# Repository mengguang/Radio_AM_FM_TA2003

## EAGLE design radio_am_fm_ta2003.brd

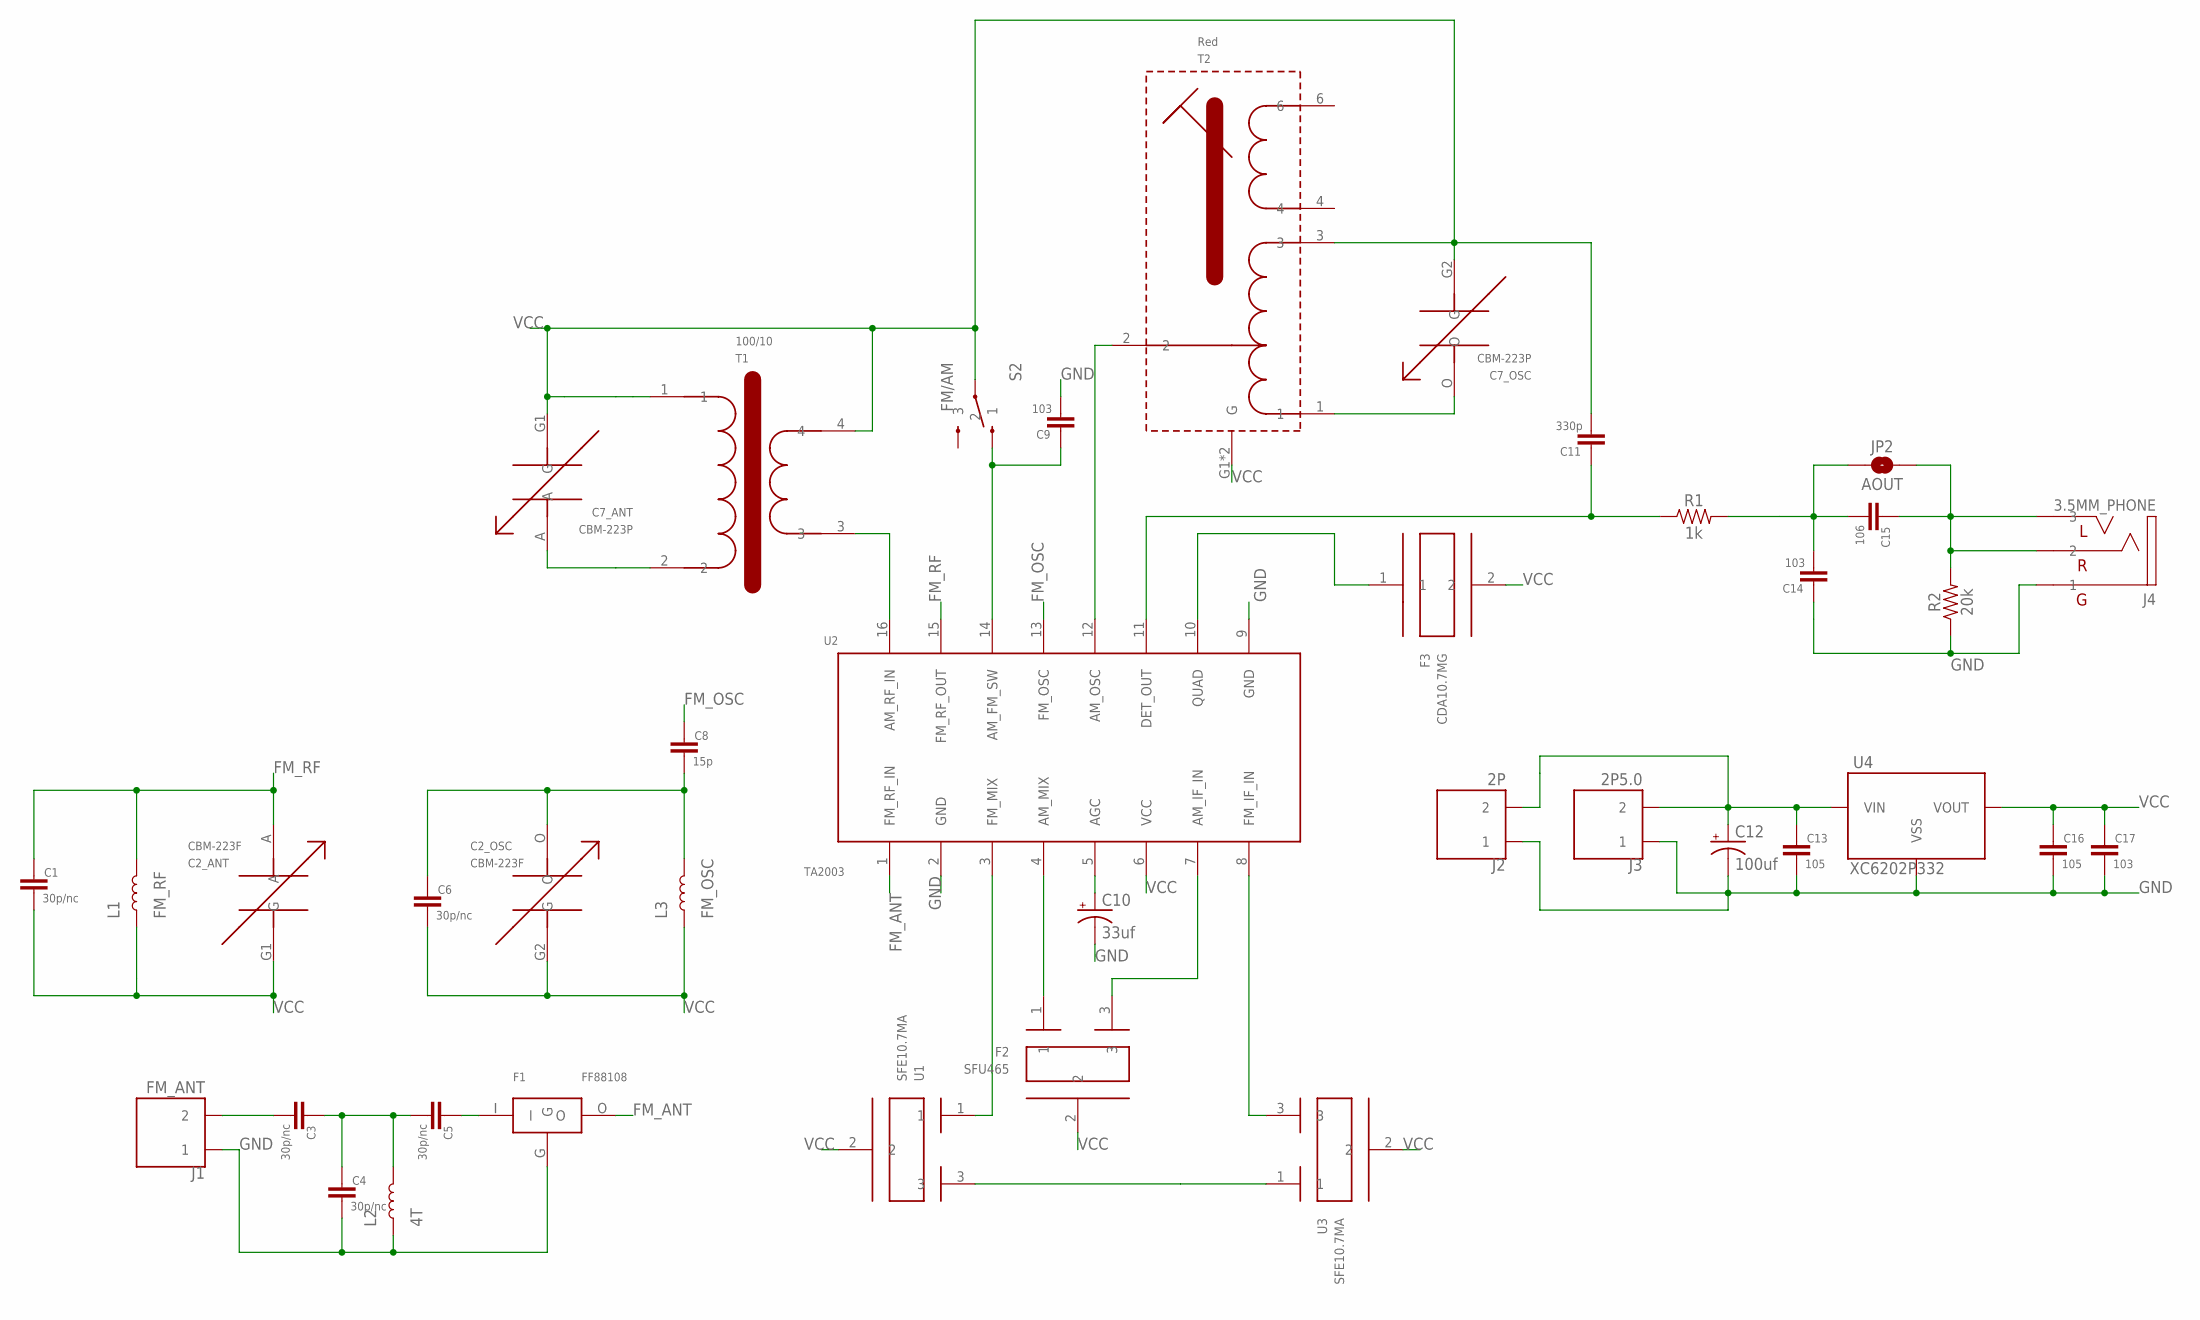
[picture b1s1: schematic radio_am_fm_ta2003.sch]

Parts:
C1, C3, C4, C5, C6: 30p/nc; C0603
C2: CBM-223F; CBM-223P
C7: CBM-223P
C8: 15p; C0603
C9, C14, C17: 103; C0603
C10: 33uf; CAP_2MM
C11: 330p; C0603
C12: 100uf; CAP_2.5MM
C13, C16: 105; C0603
C15: 106; C0603
F1: FF88108
F2: SFU465
F3: CDA10.7MG
J1: FM_ANT; 2P_2.54MM
J2: 2P; 2P_2.54MM
J3: 2P5.0; 2P_5.08MM
J4: 3.5MM_PHONE; 3.5MM
JP2: AOUT; SMT-JUMPER_2_NO_SILK
L1: FM_RF; VLU0810
L2: 4T; VLU0810
L3: FM_OSC; VLU0810
R1: 1k; R0603
R2: 20k; R0603
S2: FM/AM; L12.1_W5.6
T1: 100/10; AM_ANT_COIL
T2: Red; 42IF1XX
U1, U3: SFE10.7MA
U2: TA2003; DIP16
U4: XC6202P332; SOT-23-3

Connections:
FM_ANT: F1.O, U2.1 (FM_RF_IN)
FM_OSC: C8.1, U2.13 (FM_OSC)
FM_OSC1: C2.O, C6.1, C8.2, L3.- (2)
FM_RF: C1.1, C2.A, L1.- (2), U2.15 (FM_RF_OUT)
GND: C4.2, C9.2, C10.-, C12.-, C13.2, C14.1, C16.2, C17.2, F1.G, J1.1, J2.1, J3.L (1), J4.P$1 (1), L2.+ (1), R2.1, U2.2 (GND), U2.9 (GND), U4.3 (VSS)
unnamed: C7.O, T2.1
unnamed: T1.3, U2.16 (AM_RF_IN)
unnamed: C7.A, T1.2
unnamed: T2.2, U2.12 (AM_OSC)
unnamed: C11.1, R1.1, U2.11 (DET_OUT)
unnamed: C9.1, S2.1, U2.14 (AM_FM_SW)
unnamed: C10.+, U2.5 (AGC)
unnamed: F2.1, U2.4 (AM_MIX)
unnamed: F2.3, U2.7 (AM_IF_IN)
unnamed: U1.1, U2.3 (FM_MIX)
unnamed: U2.8 (FM_IF_IN), U3.3
unnamed: C15.1, J4.P$2 (2), J4.P$3 (3), JP2.2, R2.2
unnamed: U1.3, U3.1
unnamed: F3.1, U2.10 (QUAD)
unnamed: C3.1, C4.1, C5.2, L2.- (2)
unnamed: C3.2, J1.2
unnamed: C14.2, C15.2, JP2.1, R1.2
unnamed: C5.1, F1.I
unnamed: C12.+, C13.1, J2.2, J3.N (2), U4.2 (VIN)
VCC: C1.2, C2.G1 (G), C2.G2 (G), C6.2, C7.G1 (G), C7.G2 (G), C11.2, C16.1, C17.1, F2.2, F3.2, L1.+ (1), L3.+ (1), S2.2, T1.1, T1.4, T2.3, T2.G1 (G), T2.G2 (G), U1.2, U2.6 (VCC), U3.2, U4.1 (VOUT)

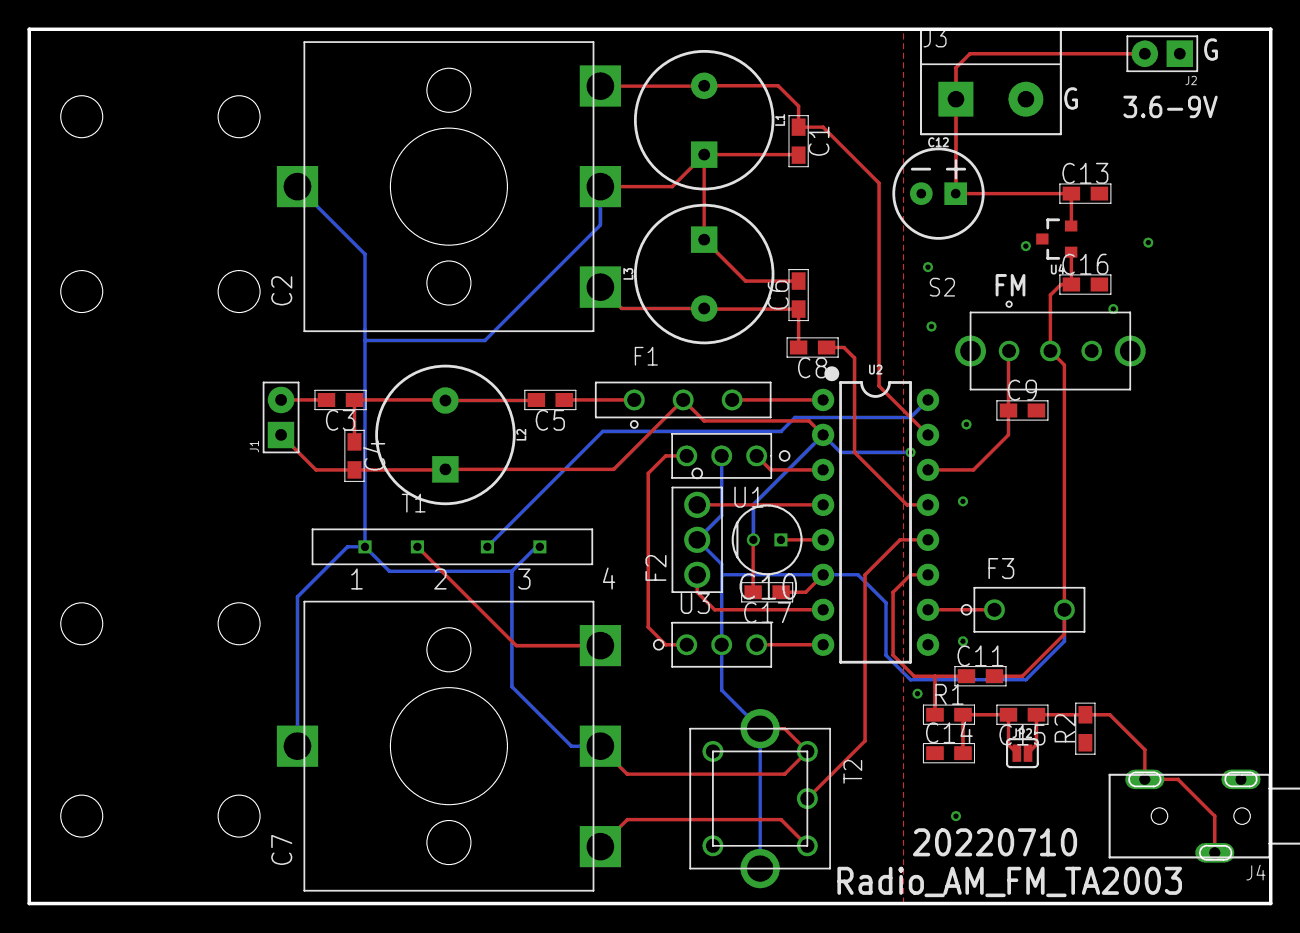
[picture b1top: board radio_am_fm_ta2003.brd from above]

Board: 2 copper layers, 90.2 x 63.5 mm, 37 parts (0 on the bottom side), 25 nets.

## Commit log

2022-07-10 20220710

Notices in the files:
parts and their libraries:
SparkFun-Jumpers: Licensing: Creative Commons ShareAlike 4.0 International - https://creativecommons.org/licenses/by-sa/4.0
